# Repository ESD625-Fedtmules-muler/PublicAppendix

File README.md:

# PublicAppendix
Public Appendix for the 6th semester project. Consisting of test data. In these folder the following can be found

 - **Antenna_measurements**: The measured antenna s-parameters \& and radiation patterns.
 - **Inventor**: The CAD files used for this project.
 - **Meshing_Firmware**: A separate git repository including the different branches of the developed mesh firmware and network stack.
 - **Monte_carl_sim**: A separate git repository showing all branches of the software used for simulating antenna parameters.
 - **Test**: The raw testdata from the physical tests along with a javascript plotter to genereate the graphs illustrated in chapter 6.

All content including subdirectories can be downloaded by
```console
git clone --recurse-submodules git@github.com:ESD625-Fedtmules-muler/PublicAppendix.git
```

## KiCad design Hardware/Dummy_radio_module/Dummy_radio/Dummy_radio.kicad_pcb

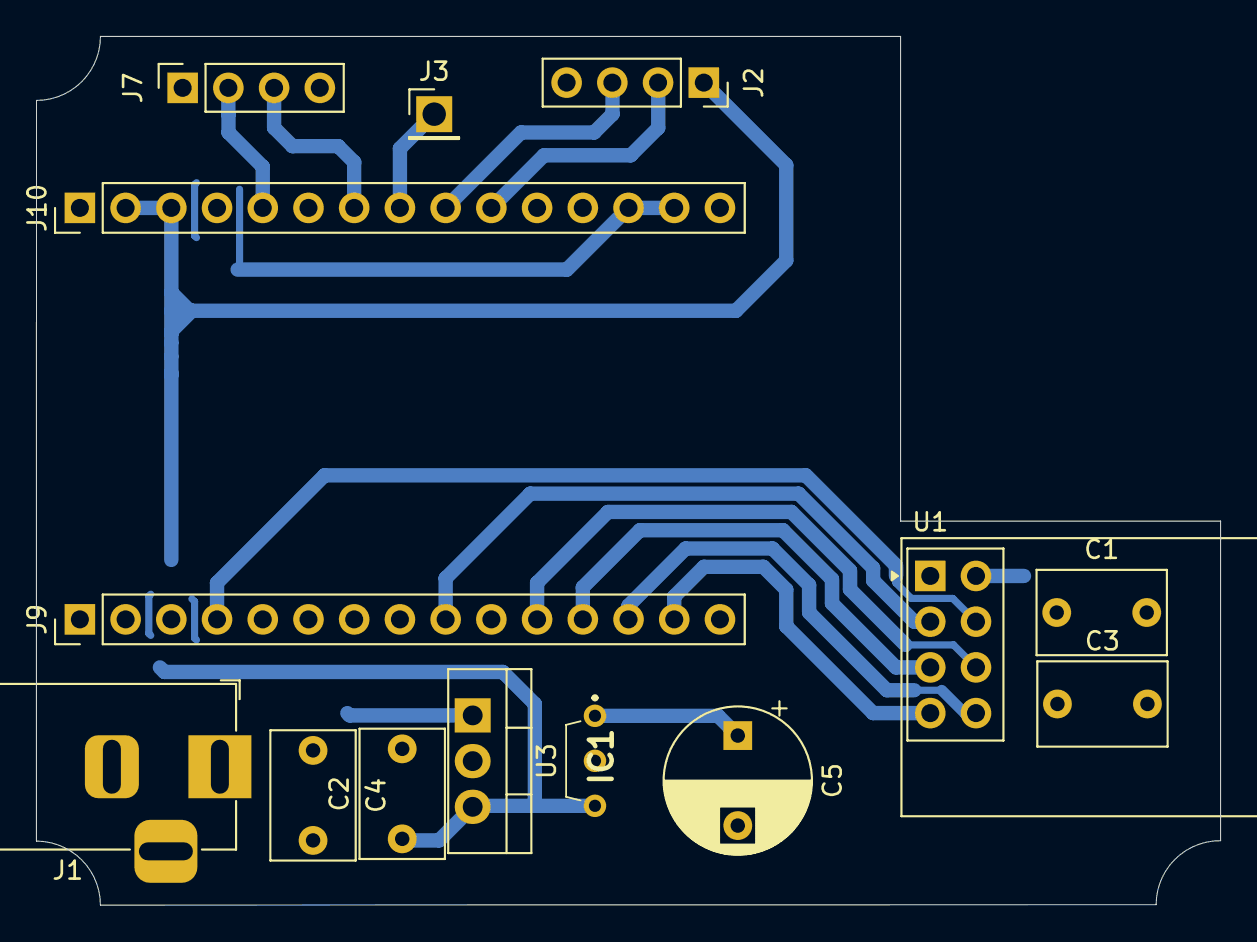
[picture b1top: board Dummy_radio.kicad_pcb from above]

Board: 2 copper layers, 65.8 x 48.3 mm, 14 parts (0 on the bottom side), 16 nets.

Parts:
C1, C2: 100n; C_Rect_L7.0mm_W4.5mm_P5.00mm
C3: 100p; C_Rect_L7.0mm_W4.5mm_P5.00mm
C4: 330n; C_Rect_L7.0mm_W4.5mm_P5.00mm
C5: 10u; CP_Radial_D8.0mm_P5.00mm
IC1: LE33CZ-TR; LE33CZTR
J1: Barrel_Jack_MountingPin; BarrelJack_Horizontal
J2: GPS_header; PinSocket_1x04_P2.54mm_Vertical
J3: Conn_01x01_Pin; PinHeader_1x01_P2.54mm_Vertical
J7: Compass; PinSocket_1x04_P2.54mm_Vertical
J9, J10: Conn_01x15; PinHeader_1x15_P2.54mm_Vertical
U1: NRF24L01_Breakout; nRF24L01_Breakout
U3: L7805; TO-220-3_Vertical

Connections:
+3.3V_RF: C1.1, C3.1, C5.1, IC1.1 (VOUT), U1.2 (VCC)
+3V3: J7.1, J10.13, J10.14
+5V: C2.1, IC1.3 (VIN), J2.1, J10.2, J10.3, U3.3 (OUT)
/CE: J9.9, U1.3 (CE)
/CSN: J9.4, U1.4 (~CSN)
/GPS.RX: J2.3, J10.9
/GPS.TX: J2.2, J10.10
/IRQ: J9.13, U1.8 (IRQ)
/MISO: J9.14, U1.7 (MISO)
/MOSI: J9.11, U1.6 (MOSI)
/PPS: J3.1 (Pin_1_1), J10.8
/SCK: J9.12, U1.5 (SCK)
/SCL: J7.2, J10.5
/SDA: J7.3, J10.7
GND: C1.2, C2.2, C3.2, C4.2, C5.2, IC1.2 (GND), J1.2, J1.3, J2.4, J7.4, J9.1, J9.2, J9.5, J9.8, J9.10, J9.15, J10.1, J10.6, J10.11, J10.15, U1.1 (GND), U3.2 (GND)
unnamed: C4.1, J1.1, U3.1 (IN)

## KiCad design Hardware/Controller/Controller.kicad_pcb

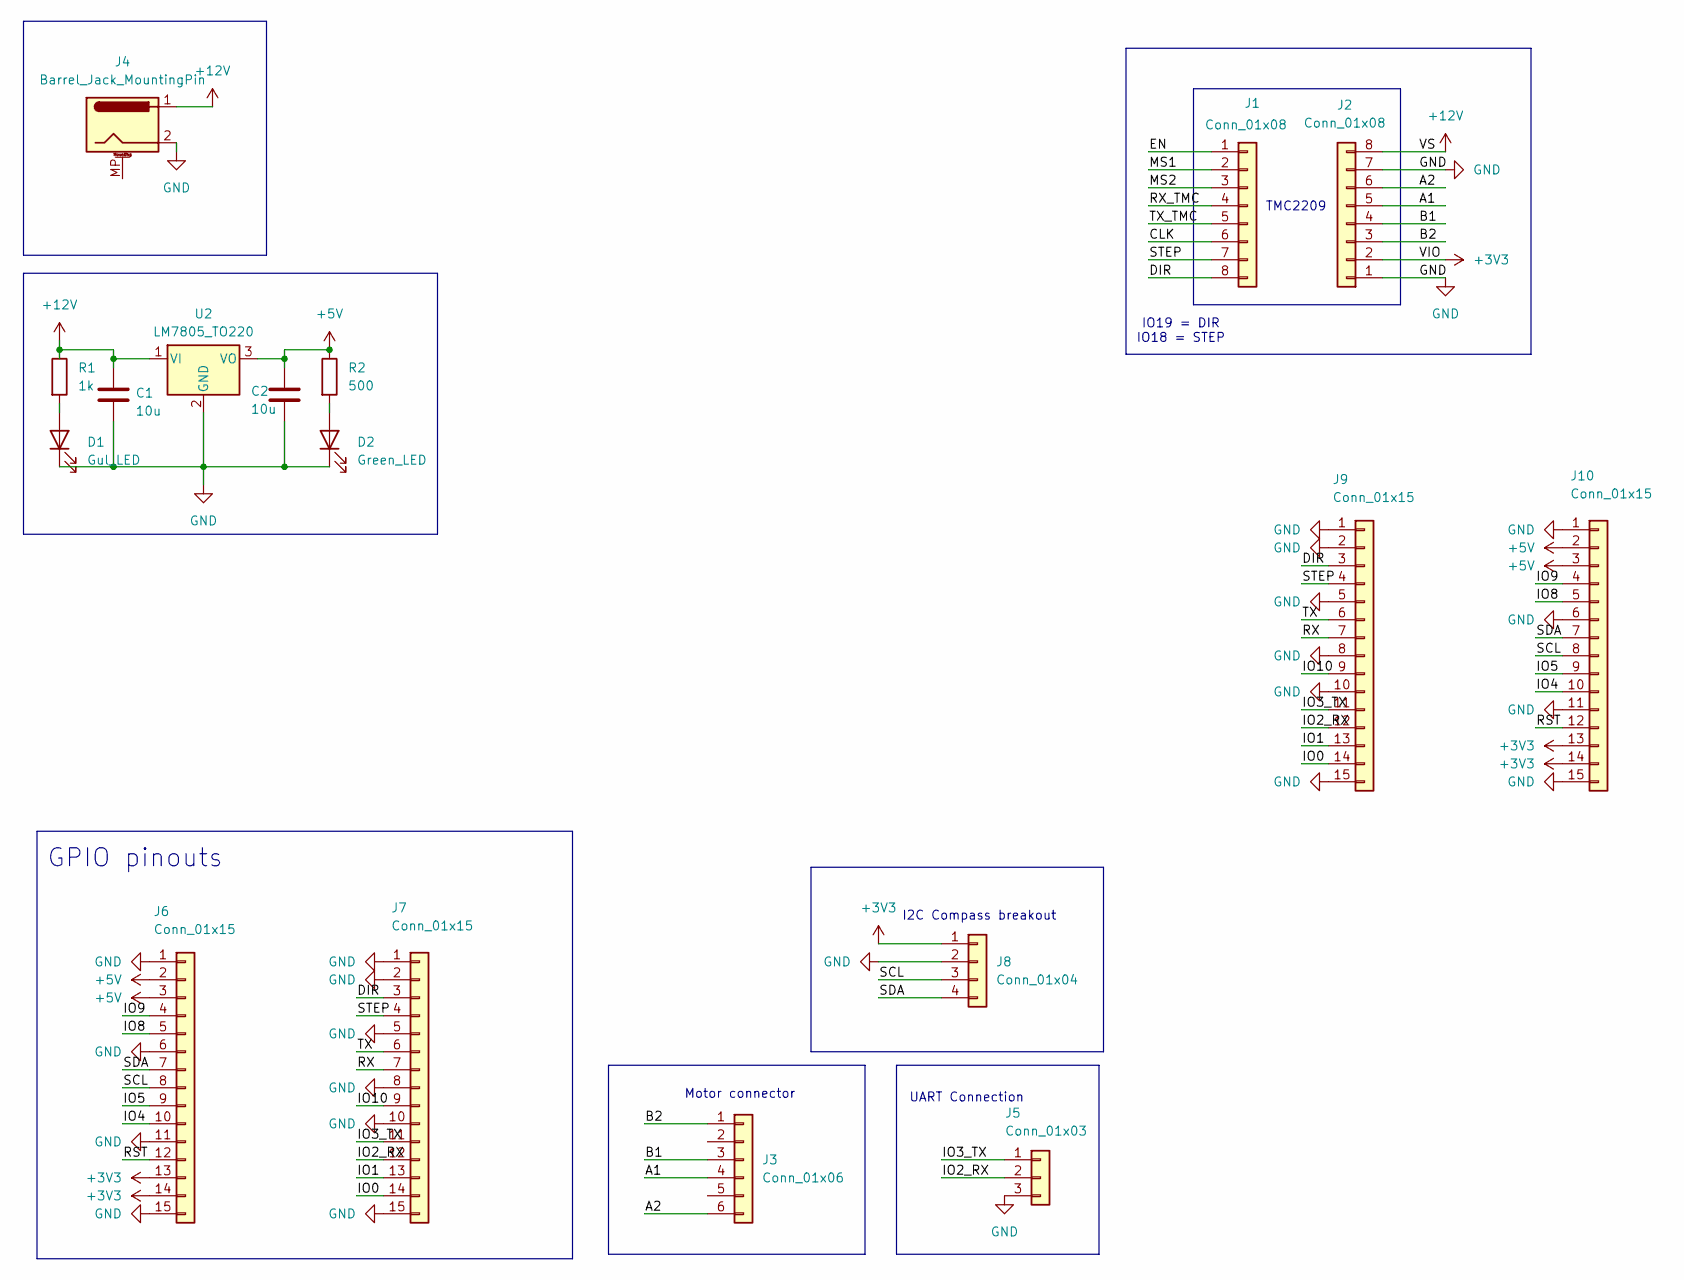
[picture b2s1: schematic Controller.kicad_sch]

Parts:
C1, C2: 10u; C_Radial_D5.0mm_H7.0mm_P2.00mm
D1: Gul_LED; LED_D4.0mm
D2: Green_LED; LED_D4.0mm
J1, J2: Conn_01x08; PinHeader_1x08_P2.54mm_Vertical
J3: Conn_01x06; Molex_KK-254_AE-6410-06A_1x06_P2.54mm_Vertical
J4: Barrel_Jack_MountingPin; BarrelJack_Horizontal
J5: Conn_01x03; Molex_KK-254_AE-6410-03A_1x03_P2.54mm_Vertical
J6, J7, J9, J10: Conn_01x15; PinHeader_1x15_P2.54mm_Vertical
J8: Conn_01x04; Molex_KK-254_AE-6410-04A_1x04_P2.54mm_Vertical
R1: 1k; R_Axial_DIN0207_L6.3mm_D2.5mm_P10.16mm_Horizontal
R2: 500; R_Axial_DIN0207_L6.3mm_D2.5mm_P10.16mm_Horizontal
U2: LM7805_TO220; TO-220-3_Horizontal_TabDown

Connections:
+3V3: J2.2, J6.13, J6.14, J8.1, J10.13, J10.14
+5V: C2.1, J6.2, J6.3, J10.2, J10.3, R2.1, U2.3 (VO)
+12V: C1.1, J2.8, J4.1, R1.1, U2.1 (VI)
/A1: J2.5, J3.4
/A2: J2.6, J3.6
/B1: J2.4, J3.3
/B2: J2.3, J3.1
/CLK: J1.6
/DIR: J1.8, J7.3, J9.3
/EN: J1.1
/IO0: J7.14, J9.14
/IO1: J7.13, J9.13
/IO2_RX: J5.2, J7.12, J9.12
/IO3_TX: J5.1, J7.11, J9.11
/IO4: J6.10, J10.10
/IO5: J6.9, J10.9
/IO8: J6.5, J10.5
/IO9: J6.4, J10.4
/IO10: J7.9, J9.9
/MS1: J1.2
/MS2: J1.3
/RST: J6.12, J10.12
/RX: J7.7, J9.7
/RX_TMC: J1.4
/SCL: J6.8, J8.3, J10.8
/SDA: J6.7, J8.4, J10.7
/STEP: J1.7, J7.4, J9.4
/TX: J7.6, J9.6
/TX_TMC: J1.5
GND: C1.2, C2.2, D1.1 (K), D2.1 (K), J2.1, J2.7, J4.2, J5.3, J6.1, J6.6, J6.11, J6.15, J7.1, J7.2, J7.5, J7.8, J7.10, J7.15, J8.2, J9.1, J9.2, J9.5, J9.8, J9.10, J9.15, J10.1, J10.6, J10.11, J10.15, U2.2 (GND)
unnamed: D1.2 (A), R1.2
unnamed: D2.2 (A), R2.2

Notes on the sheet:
I2C Compass breakout
GPIO pinouts
UART Connection
TMC2209
IO19 = DIR IO18 = STEP
Motor connector

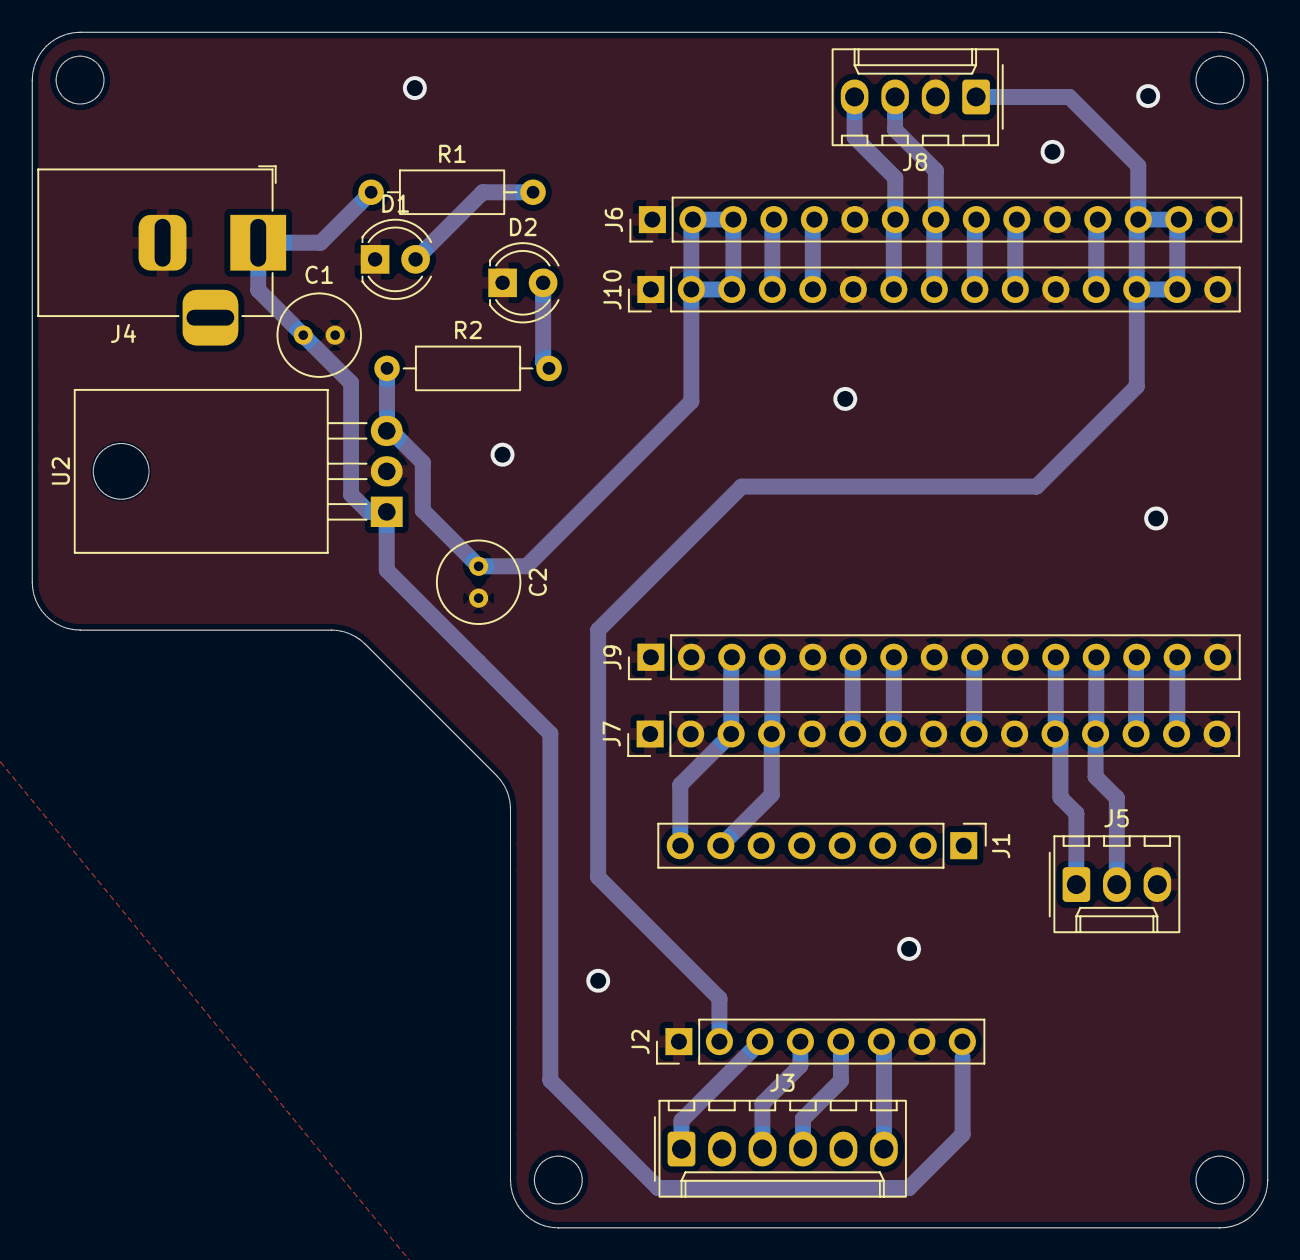
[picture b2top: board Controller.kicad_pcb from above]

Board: 2 copper layers, 77.5 x 75.0 mm, 17 parts (0 on the bottom side), 26 nets.

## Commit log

2026-05-26 Smider masse lort ind
2026-05-26 Added mc as submodule
2026-05-26 Router firmware
2026-05-26 Ryddede op efter mikkel
2026-05-26 Transciever
2026-05-26 Dummy radio
2026-05-26 added s param measurement
2026-05-27 Expand README to include additional project details
2026-05-27 Update README with detailed folder contents
    Expanded the README to include details about the contents of the project folders.
2026-05-27 Include git clone command for submodules
    Added instructions for cloning the repository with submodules.
